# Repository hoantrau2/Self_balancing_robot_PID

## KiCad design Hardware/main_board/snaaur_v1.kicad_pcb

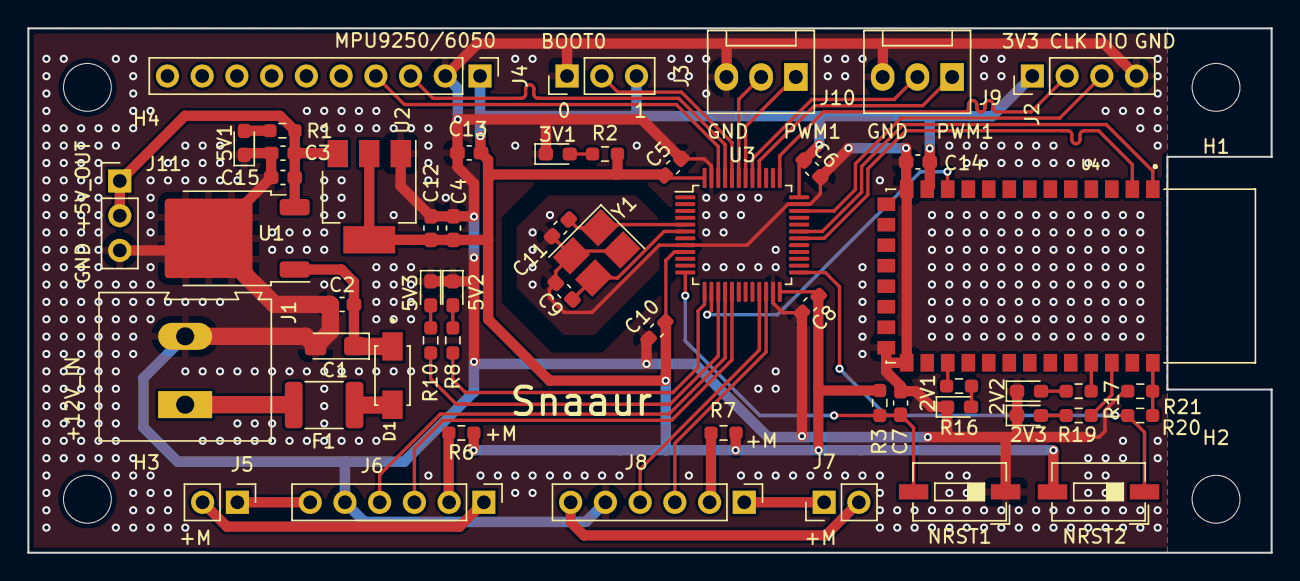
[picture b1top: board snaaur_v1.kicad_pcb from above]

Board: 2 copper layers, 90.9 x 38.4 mm, 58 parts (0 on the bottom side), 45 nets.

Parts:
2V1: RED; LED_0603_1608Metric_Pad1.05x0.95mm_HandSolder
2V2: YELLOW; LED_0603_1608Metric_Pad1.05x0.95mm_HandSolder
2V3: GREEN; LED_0603_1608Metric_Pad1.05x0.95mm_HandSolder
3V1, 5V1, 5V2, 5V3: LED; LED_0603_1608Metric_Pad1.05x0.95mm_HandSolder
C1: 1u, 16V; CP_EIA-3216-18_Kemet-A_Pad1.58x1.35mm_HandSolder
C2, C15: 100nF,50V; C_0603_1608Metric_Pad1.08x0.95mm_HandSolder
C3, C4, C5, C6, C7, C8, C10, C13, C14: 100n; C_0603_1608Metric_Pad1.08x0.95mm_HandSolder
C9, C11: 22p; C_0603_1608Metric_Pad1.08x0.95mm_HandSolder
C12: 4.7u; C_0603_1608Metric_Pad1.08x0.95mm_HandSolder
D1: RS1M; DIOM4330X250N
F1: Fuse; Fuse_1812_4532Metric_Pad1.30x3.40mm_HandSolder
H1, H2, H3, H4: MountingHole; MountingHole_3.5mm
J1: POWER; TerminalBlock_Altech_AK300-2_P5.00mm
J2: Debug; PinHeader_1x04_P2.54mm_Vertical
J3: boot; PinHeader_1x03_P2.54mm_Vertical
J4: MPU6050; PinHeader_1x10_P2.54mm_Vertical
J5, J7: Conn_01x02_Pin; PinHeader_1x02_P2.54mm_Vertical
J6: Motor1; PinHeader_1x06_P2.54mm_Vertical
J8: Motor2; PinHeader_1x06_P2.54mm_Vertical
J9: PWM1; FanPinHeader_1x03_P2.54mm_Vertical
J10: PWM2; FanPinHeader_1x03_P2.54mm_Vertical
J11: 5V_OUT; PinHeader_1x03_P2.54mm_Vertical
NRST1, NRST2: SW_Push; SW_DIP_SPSTx01_Slide_6.7x4.1mm_W6.73mm_P2.54mm_LowProfile_J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
R1: 1k; R_0603_1608Metric_Pad0.98x0.95mm_HandSolder
R2, R8, R10: 330; R_0603_1608Metric_Pad0.98x0.95mm_HandSolder
R3, R21: 10k; R_0603_1608Metric_Pad0.98x0.95mm_HandSolder
R6, R7: 0; R_0603_1608Metric_Pad0.98x0.95mm_HandSolder
R16, R17, R19: 470; R_0603_1608Metric_Pad0.98x0.95mm_HandSolder
R20: 2.2k; R_0603_1608Metric_Pad0.98x0.95mm_HandSolder
U1: L7805; TO-252-2
U2: AMS1117-3.3; SOT-223-3_TabPin2
U3: STM32F103C8Tx; LQFP-48_7x7mm_P0.5mm
U4: HC-05; XCVR_HC-05
Y1: Crystal; Crystal_SMD_3225-4Pin_3.2x2.5mm_HandSoldering

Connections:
+3.3V: C4.2, C5.1, C6.1, C8.1, C10.1, C12.1, C13.1, C14.2, J2.1, J3.3, J4.1, NRST2.2, R2.1, R3.1, R6.1, R7.1, U2.2 (VO), U3.9 (VDDA), U3.24 (VDD), U3.36 (VDD), U3.48 (VDD), U4.12 (3.3_VCC)
+5V: C3.2, C15.2, J11.1, J11.2, R1.1, U1.3 (OUT), U2.3 (VI)
+12V: F1.1, J1.1
+M1: J5.2, J6.1
+M2: J7.1, J8.1
-M1: J5.1, J6.6
-M2: J7.2, J8.6
/PWM1_CH1: J9.1, U3.40 (PB4)
/PWM2_CH1: J10.1, U3.42 (PB6)
BLE_ENB: NRST2.1, R20.1, U3.25 (PB12)
BLUE_RESET: U3.14 (PA4), U4.11 (~RESETB)
BLUE_RX: U3.30 (PA9), U4.2 (UART-RX)
BLUE_TX: U3.31 (PA10), U4.1 (UART-TX)
BOOT0: J3.2, U3.44 (BOOT0)
GND: 2V1.1 (K), 2V2.1 (K), 2V3.1 (K), 3V1.1 (K), 5V1.1 (K), 5V2.1 (K), 5V3.1 (K), C1.2, C2.1, C3.1, C4.1, C5.2, C6.2, C7.1, C8.2, C9.2, C10.2, C11.1, C12.2, C13.2, C14.1, C15.1, J1.2, J2.4, J3.1, J4.2, J6.5, J8.5, J9.3, J10.3, J11.3, NRST1.1, R21.2, U1.2 (GND), U2.1 (GND), U3.8 (VSSA), U3.23 (VSS), U3.35 (VSS), U3.47 (VSS), U4.13 (GND), U4.21 (GND), U4.22 (GND), Y1.2, Y1.4
IMU_SCL: J4.3, U3.45 (PB8)
IMU_SDA: J4.4, U3.46 (PB9)
LED1: R8.1, U3.13 (PA3)
LED2: R10.1, U3.15 (PA5)
NRST: C7.2, NRST1.2, R3.2, U3.12 (PA2)
unnamed: 2V1.2 (A), R16.2
unnamed: 2V2.2 (A), R17.2
unnamed: 2V3.2 (A), R19.2
unnamed: 3V1.2 (A), R2.2
unnamed: 5V1.2 (A), R1.2
unnamed: 5V2.2 (A), R8.2
unnamed: 5V3.2 (A), R10.2
unnamed: D1.A, F1.2
unnamed: J6.2, R6.2
unnamed: J8.2, R7.2
unnamed: J9.2, U3.41 (PB5)
unnamed: J10.2, U3.43 (PB7)
unnamed: C1.1, C2.2, D1.C, U1.1 (IN)
unnamed: R16.1, U4.24 (PIO[1])
unnamed: R17.1, U4.31 (PIO[8])
unnamed: R19.1, U4.32 (PIO[9])
unnamed: R20.2, R21.1, U4.34 (PIO[11])
OSC1: C11.2, U3.5 (PD0), Y1.1
OSC2: C9.1, U3.6 (PD1), Y1.3
SWCLK: J2.2, U3.37 (PA14)
SWDIO: J2.3, U3.34 (PA13)
enc_in_1a: J6.4, U3.16 (PA6)
enc_in_1b: J6.3, U3.17 (PA7)
enc_in_2a: J8.4, U3.21 (PB10)
enc_in_2b: J8.3, U3.22 (PB11)

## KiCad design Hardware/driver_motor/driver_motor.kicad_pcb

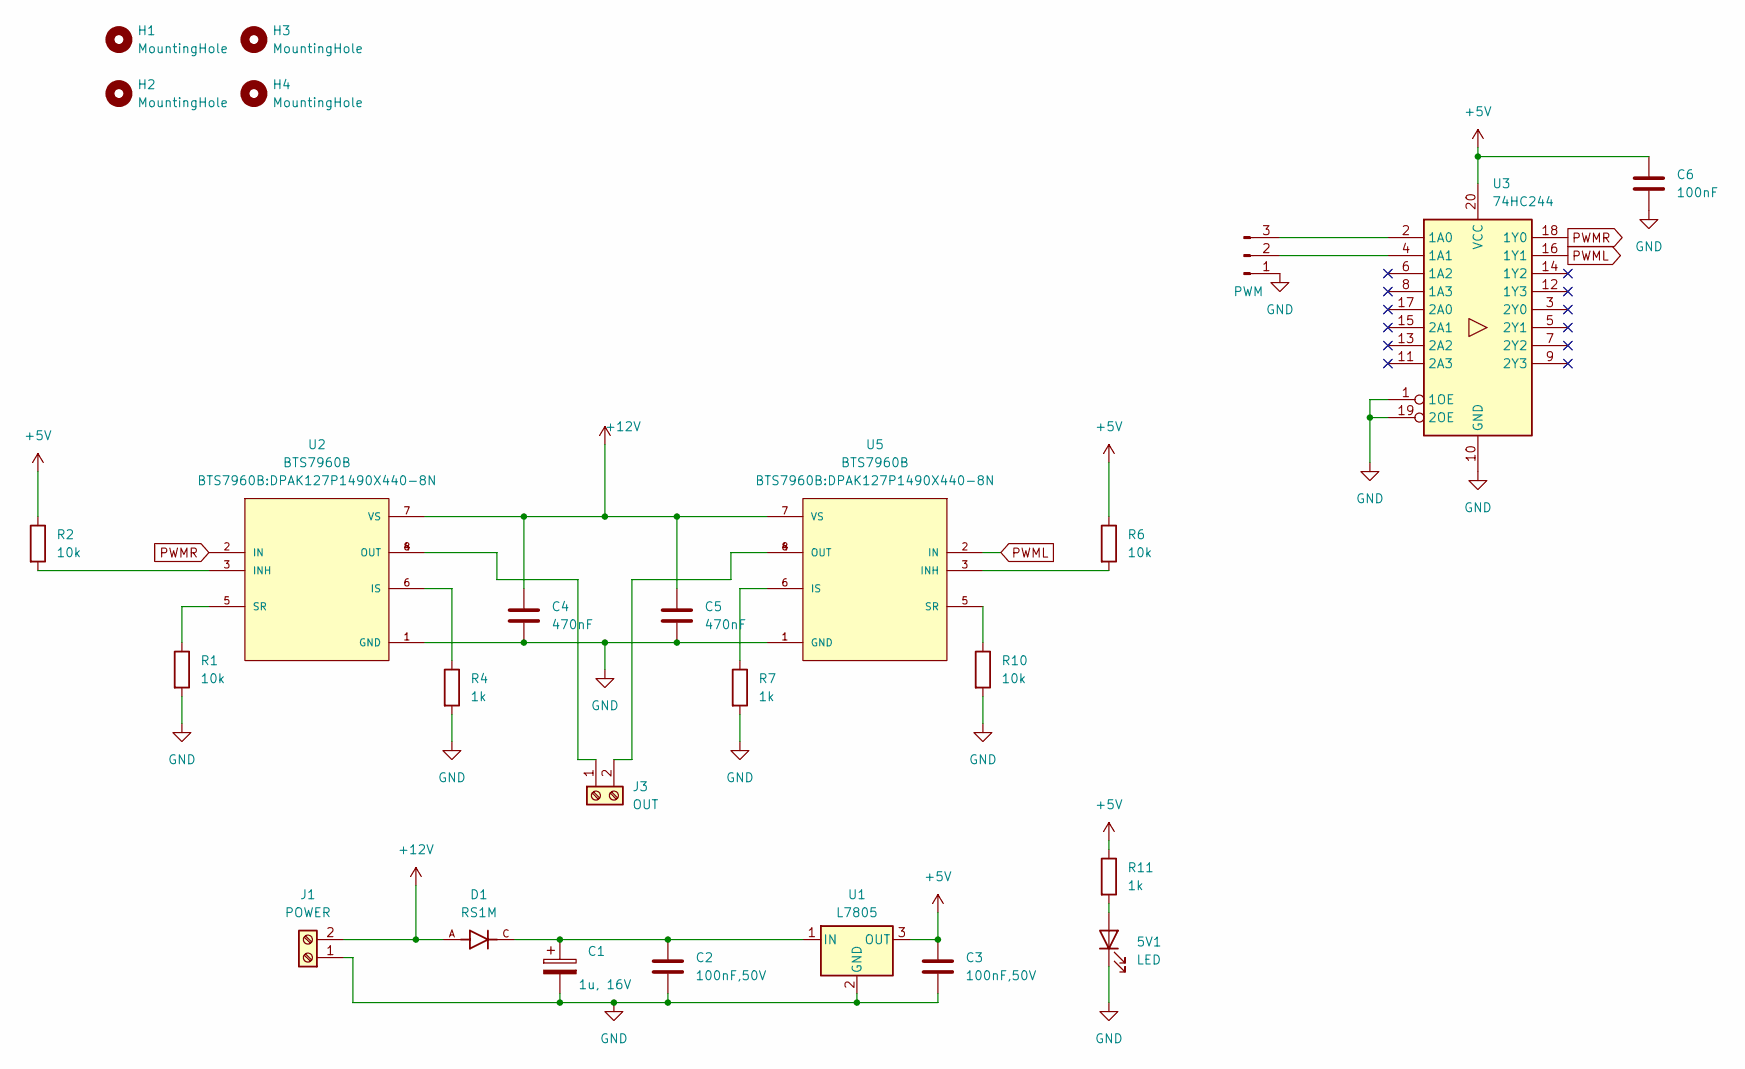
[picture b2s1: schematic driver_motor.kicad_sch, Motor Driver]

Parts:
5V1: LED; LED_0603_1608Metric_Pad1.05x0.95mm_HandSolder
C1: 1u, 16V; CP_EIA-3216-18_Kemet-A_Pad1.58x1.35mm_HandSolder
C2, C3: 100nF,50V; C_0603_1608Metric_Pad1.08x0.95mm_HandSolder
C4, C5: 470nF; C_0603_1608Metric_Pad1.08x0.95mm_HandSolder
C6: 100nF; C_0603_1608Metric_Pad1.08x0.95mm_HandSolder
D1: RS1M; DIOM4330X250N; PARTREV 1.0
H1, H2, H3, H4: MountingHole; MountingHole_3.5mm
J1: POWER; TerminalBlock_Altech_AK300-2_P5.00mm
J2: PWM; FanPinHeader_1x03_P2.54mm_Vertical
J3: OUT; TerminalBlock_Altech_AK300-2_P5.00mm
R1, R2, R6, R10: 10k; R_0603_1608Metric_Pad0.98x0.95mm_HandSolder
R4, R7, R11: 1k; R_0603_1608Metric_Pad0.98x0.95mm_HandSolder
U1: L7805; TO-252-2
U2, U5: BTS7960B; DPAK127P1490X440-8N; PARTREV 1.1
U3: 74HC244; SOIC127P1030X265-20N

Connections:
+5V: C3.2, C6.1, R2.1, R6.1, R11.1, U1.3 (OUT), U3.20 (VCC)
+12V: C4.2, C5.1, D1.A, J1.2, U2.7 (VS), U5.7 (VS)
GND: 5V1.1 (K), C1.2, C2.1, C3.1, C4.1, C5.2, C6.2, J1.1, J2.1, R1.2, R4.2, R7.2, R10.2, U1.2 (GND), U2.1 (GND), U3.1 (1OE), U3.10 (GND), U3.19 (2OE), U5.1 (GND)
unnamed: 5V1.2 (A), R11.2
unnamed: J2.2, U3.4 (1A1)
unnamed: J2.3, U3.2 (1A0)
unnamed: J3.1, U2.4 (OUT), U2.8 (OUT)
unnamed: J3.2, U5.4 (OUT), U5.8 (OUT)
unnamed: C1.1, C2.2, D1.C, U1.1 (IN)
unnamed: R2.2, U2.3 (INH)
unnamed: R4.1, U2.6 (IS)
unnamed: R1.1, U2.5 (SR)
unnamed: R6.2, U5.3 (INH)
unnamed: R7.1, U5.6 (IS)
unnamed: R10.1, U5.5 (SR)
PWML: U3.16 (1Y1), U5.2 (IN)
PWMR: U2.2 (IN), U3.18 (1Y0)

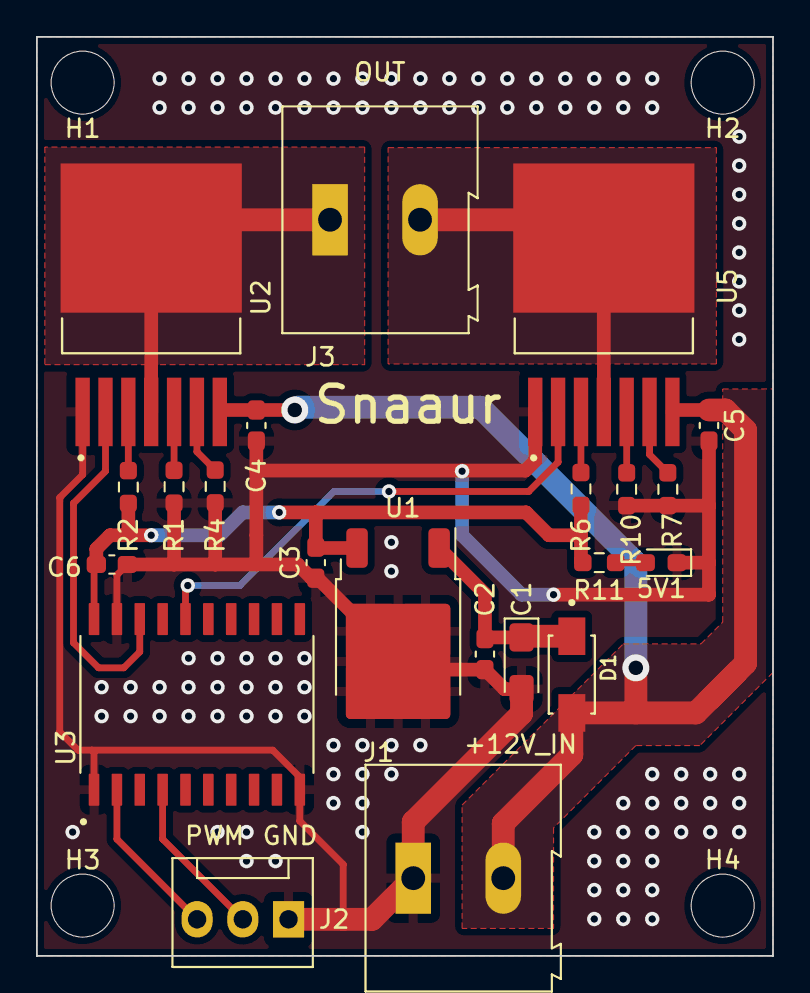
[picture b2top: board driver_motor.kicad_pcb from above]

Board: 2 copper layers, 40.9 x 51.1 mm, 26 parts (0 on the bottom side), 17 nets.

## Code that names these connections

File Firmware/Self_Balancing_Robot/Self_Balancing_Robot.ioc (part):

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Mcu.Name=STM32F103C(8-B)Tx
Mcu.Package=LQFP48
Mcu.UserName=STM32F103C8Tx
PA10.Mode=Asynchronous
PA10.Signal=USART1_RX
PA13.Mode=Serial_Wire
PA13.Signal=SYS_JTMS-SWDIO
PA14.Mode=Serial_Wire
PA14.Signal=SYS_JTCK-SWCLK
PA3.Signal=GPIO_Output
PA5.Signal=GPIO_Output
PA9.Mode=Asynchronous
PA9.Signal=USART1_TX
PB4.Signal=S_TIM3_CH1
PB5.Signal=S_TIM3_CH2
PB6.Signal=S_TIM4_CH1
PB7.Signal=S_TIM4_CH2
PB8.Mode=I2C
PB8.Signal=I2C1_SCL
PB9.Mode=I2C
PB9.Signal=I2C1_SDA
PC13-TAMPER-RTC.Signal=GPIO_Output
PD0-OSC_IN.Mode=HSE-External-Oscillator
PD0-OSC_IN.Signal=RCC_OSC_IN
PD1-OSC_OUT.Mode=HSE-External-Oscillator
PD1-OSC_OUT.Signal=RCC_OSC_OUT
board=custom

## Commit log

2023-09-22 Use PID control algorithm
2023-09-23 reload robot operation video
2023-09-23 add some note
2023-09-23 original robot
2023-09-26 add note
2023-09-26 add flowchart
2023-10-12 add gif
